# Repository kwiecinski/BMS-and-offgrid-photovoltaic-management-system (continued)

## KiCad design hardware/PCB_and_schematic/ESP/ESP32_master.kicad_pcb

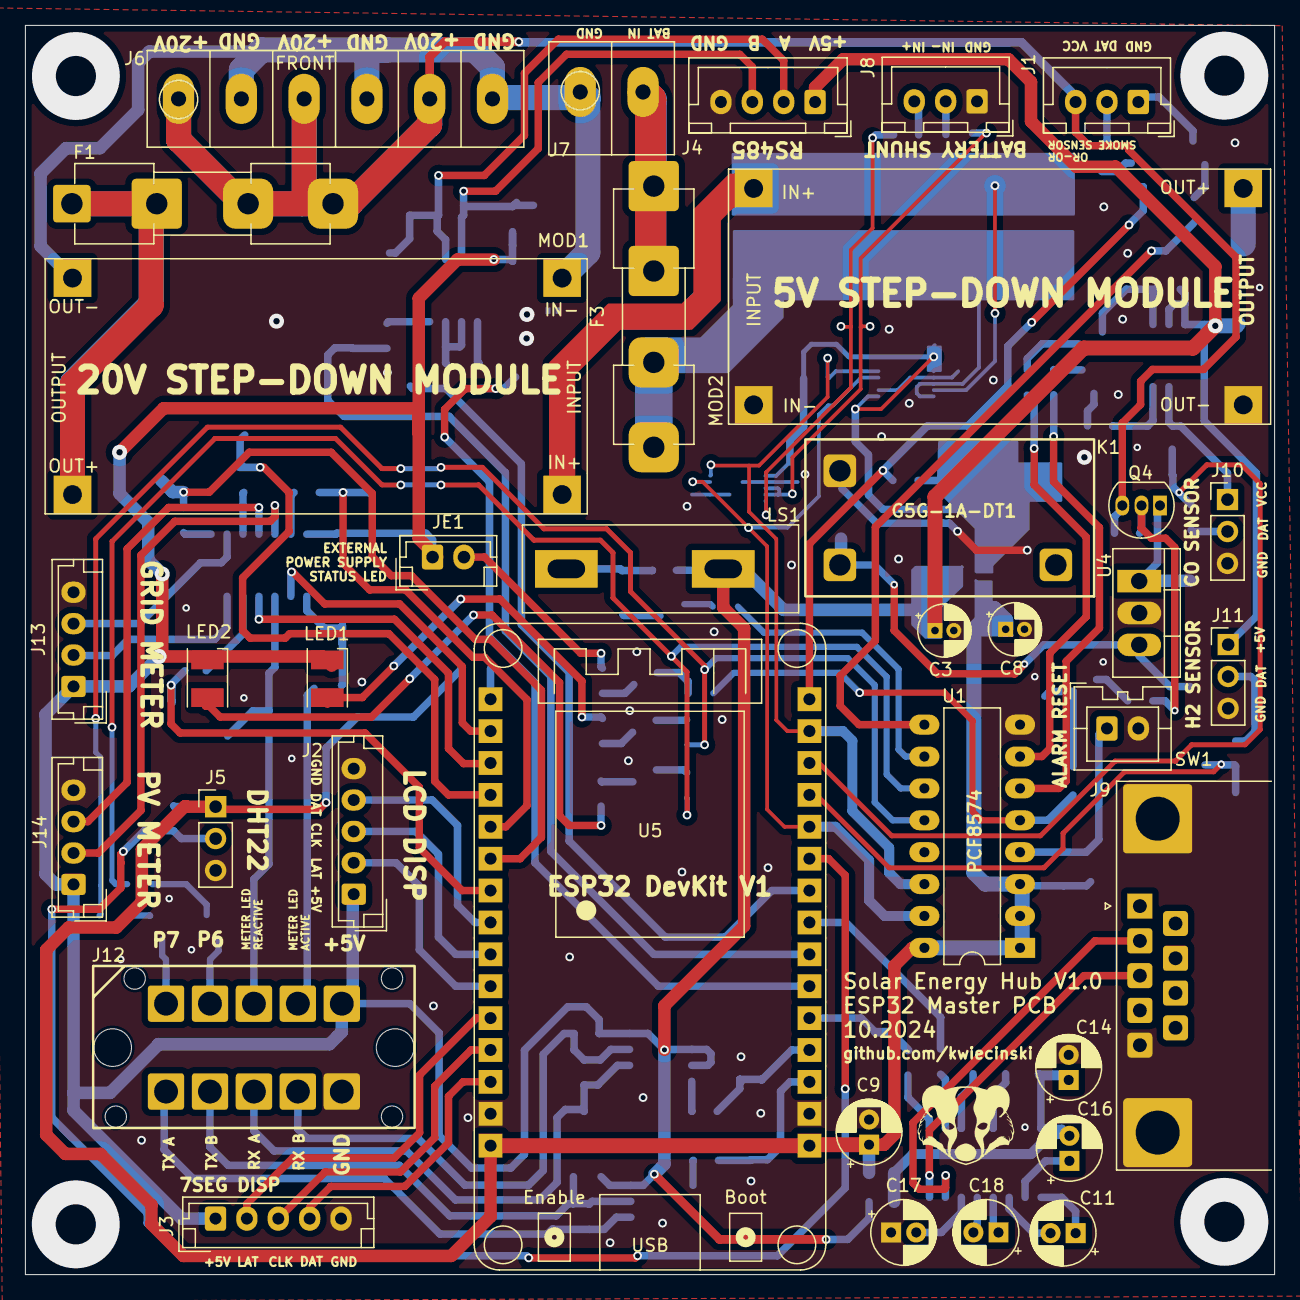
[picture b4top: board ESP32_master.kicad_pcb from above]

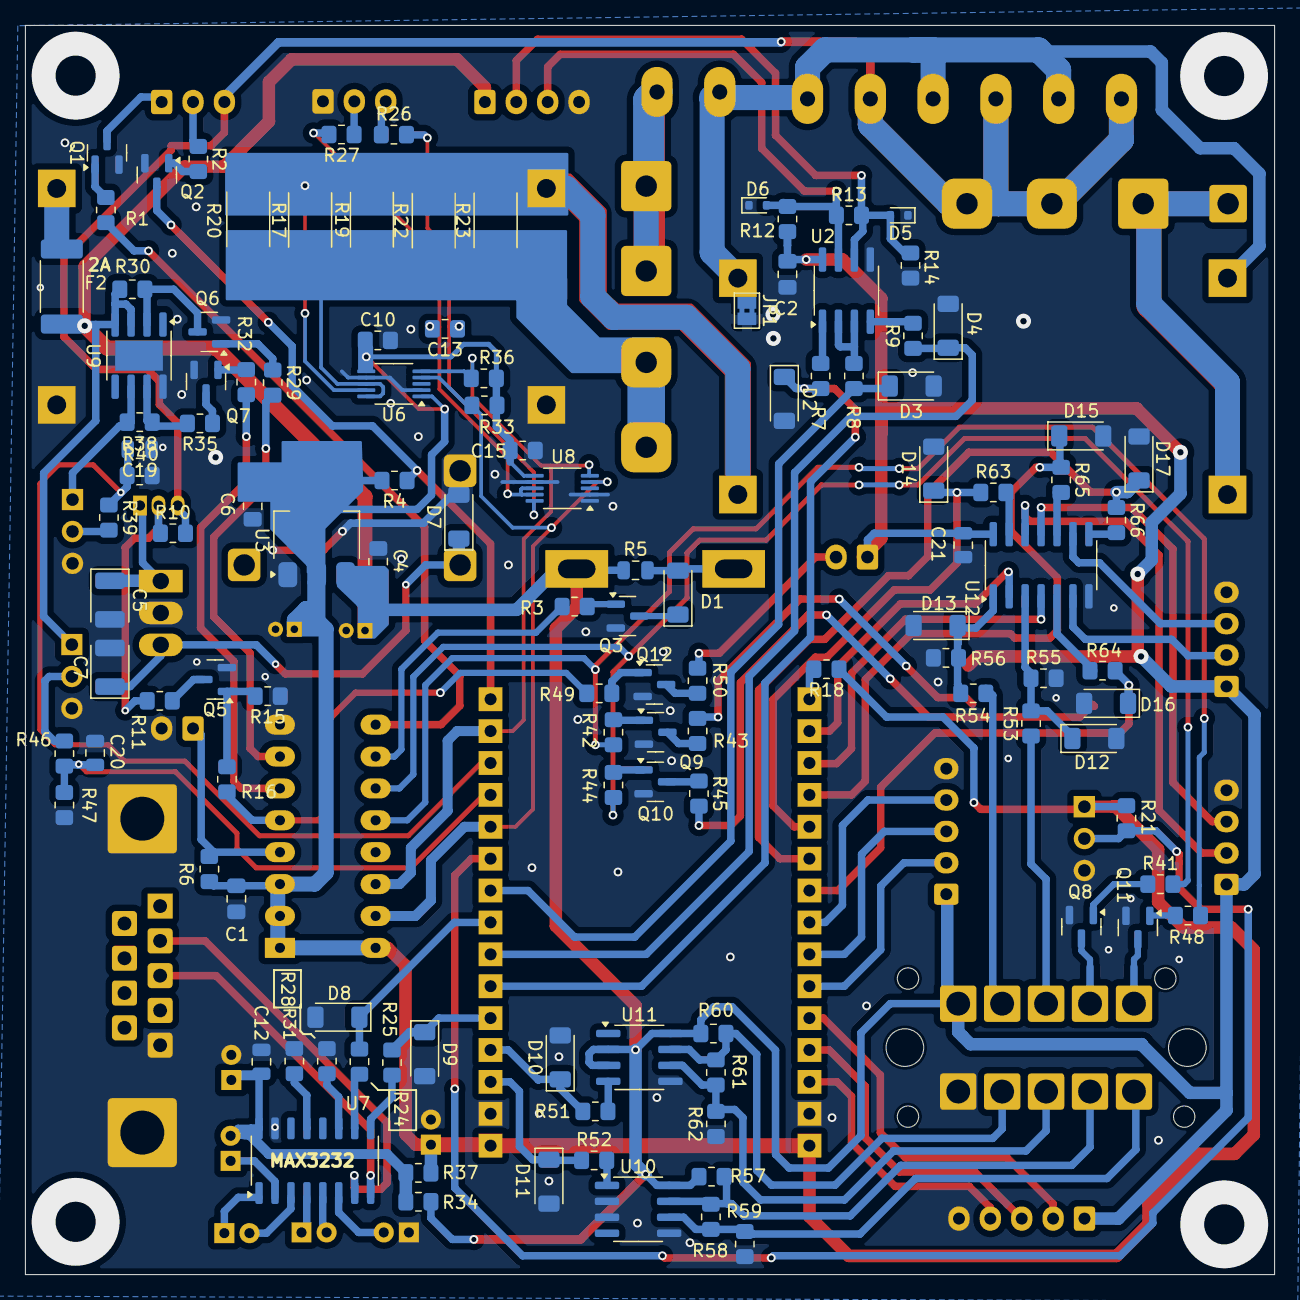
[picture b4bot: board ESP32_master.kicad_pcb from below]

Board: 2 copper layers, 99.5 x 99.5 mm, 154 parts (118 on the bottom side), 117 nets.

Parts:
C1, C2, C4, C6: 100n; C_0805_2012Metric_Pad1.18x1.45mm_HandSolder
C3: 100u; CP_Radial_D4.0mm_P1.50mm
C5: 22u/25V; CP_EIA-3528-21_Kemet-B
C7: 10u/16V; CP_EIA-3528-21_Kemet-B
C8: 22u; CP_Radial_D4.0mm_P1.50mm
C9: 22u; CP_Radial_D5.0mm_P2.00mm
C10, C15: 100n; R_0805_2012Metric_Pad1.20x1.40mm_HandSolder
C11, C16, C17, C18: 10u; CP_Radial_D5.0mm_P2.00mm
C12, C21: 100n; C_0805_2012Metric
C13: 1n; R_0805_2012Metric_Pad1.20x1.40mm_HandSolder
C14: 47u; CP_Radial_D5.0mm_P2.00mm
C19, C20: 10n; C_0805_2012Metric
D1: 1N4148; D_MiniMELF
D2, D3, D4, D8, D9, D10, D11, D14, D15, D16, D17: 3V3; D_MiniMELF
D5, D6: LESD5D5.0CT1G-MS; D_SOD-523
D7: LL4148; D_MiniMELF
D12, D13: 5V6; D_MiniMELF
F1: 2A; Fuseholder_Clip-5x20mm_Eaton_1A5601-01_Inline_P20.80x6.76mm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
F2: 2A; Fuse_2512_6332Metric_Pad1.52x3.35mm_HandSolder
F3: Fuse; Fuseholder_Clip-5x20mm_Eaton_1A5601-01_Inline_P20.80x6.76mm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
J1: OR-OR SMOKE SENSOR; JST_XH_B3B-XH-A_1x03_P2.50mm_Vertical
J2: LCD_DISP; JST_EH_B5B-EH-A_1x05_P2.50mm_Vertical
J3: 7SEG_DISP; JST_EH_B5B-EH-A_1x05_P2.50mm_Vertical
J4: RS485; JST_XH_B4B-XH-A_1x04_P2.50mm_Vertical
J5: DHT22; PinHeader_1x03_P2.54mm_Vertical
J6: DC_LINE_OUTPUT; Screw-Terminal-P6-rast-5mm-6,7x30
J7: MAIN_BATT_+24V; Screw-Terminal-P2-rast-5mm-6,7x30
J8: MAIN_BATT_SHUNT; JST_XH_B3B-XH-A_1x03_P2.50mm_Vertical
J9: DB9_Socket; DSUB-9_Female_Horizontal_P2.77x2.84mm_EdgePinOffset7.70mm_H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
J10: CO_SENSOR; PinHeader_1x03_P2.54mm_Vertical
J11: H2_SENSOR; PinHeader_1x03_P2.54mm_Vertical
J12: EXTERNAL_SIGNALS; CDDC-1,5-5-PV-3,5
J13: METER_GRID; JST_EH_B4B-EH-A_1x04_P2.50mm_Vertical
J14: METER_PV; JST_EH_B4B-EH-A_1x04_P2.50mm_Vertical
JE1: EXTERNAL_POWER_SUPPLY_STATUS; JST_EH_B2B-EH-A_1x02_P2.50mm_Vertical
JP1: Jumper_2_Bridged; SolderJumper-2_P1.3mm_Bridged2Bar_Pad1.0x1.5mm
K1: G5G-1A-DT1
LED1, LED2: LED; LED_PLCC-2_3.4x3.0mm_KA
LS1: BUZZER; Buzzer
MOD1, MOD2: LM2596-Step-Down; LM2596-Step-Down-Conv
Q1, Q2, Q3, Q5, Q8, Q9, Q10, Q11, Q12: BC817; SOT-23
Q4: BC556; TO-92_Inline
Q6, Q7: BSS138; SOT-23
R1, R2, R3, R4, R6, R11, R16, R18, R21, R30, R33, R36, R53, R54, R65, R66: 10k; R_0805_2012Metric_Pad1.20x1.40mm_HandSolder
R5: 2k; C_0805_2012Metric
R7, R8, R9, R24, R25, R51, R52, R63, R64: 4k7; R_0805_2012Metric_Pad1.20x1.40mm_HandSolder
R10, R15: 47k; R_0805_2012Metric_Pad1.20x1.40mm_HandSolder
R12, R14, R57, R59, R60, R62: 510R; R_0805_2012Metric_Pad1.20x1.40mm_HandSolder
R13, R58, R61: 120R; R_0805_2012Metric_Pad1.20x1.40mm_HandSolder
R17, R19, R20, R22, R23: 2,5mR; R_2512_6332Metric
R26, R27, R29, R32: 100R; R_0805_2012Metric_Pad1.20x1.40mm_HandSolder
R28, R31: 1k; R_0805_2012Metric_Pad1.20x1.40mm_HandSolder
R34, R37: 0R; R_0805_2012Metric_Pad1.20x1.40mm_HandSolder
R35: 1k8; R_0805_2012Metric_Pad1.20x1.40mm_HandSolder
R38, R41, R42, R44, R48, R49: 10K; R_0805_2012Metric_Pad1.20x1.40mm_HandSolder
R39, R46: 7k8; R_0805_2012Metric_Pad1.20x1.40mm_HandSolder
R40, R47: 2k2; R_0805_2012Metric_Pad1.20x1.40mm_HandSolder
R43, R45, R50: 220R; R_0805_2012Metric_Pad1.20x1.40mm_HandSolder
R55, R56: 2,4k; R_0805_2012Metric_Pad1.20x1.40mm_HandSolder
SW1: SW_Push; JST_XA_B02B-XASK-1_1x02_P2.50mm_Vertical
U1: PCF8574; DIP-16_W7.62mm_LongPads
U2: ST485; SOIC-8_3.9x4.9mm_P1.27mm
U3: AMS1117-5.0; SOT-223-3_TabPin2
U4: L7812; TO-220-3_V_Thick_Pads
U5: ESP32_DevKit_V1_DOIT; esp32_devkit_v1_doit
U6, U8: INA226; VSSOP-10_3x3mm_P0.5mm
U7: MAX3232; SO-16_3.9x9.9mm_P1.27mm
U9: UP7760; SOIC-8-1EP_3.9x4.9mm_P1.27mm_EP2.41x3.81mm
U10, U11: ST485EBDR; SOIC-8_3.9x4.9mm_P1.27mm
U12: 74HC14; SOIC-14_3.9x8.7mm_P1.27mm

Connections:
7_SEG_DISP_CLOCK: J3.3, U5.12 (IO12)
7_SEG_DISP_DATA: J3.4, U5.13 (IO13)
7_SEG_DISP_LATCH: J3.2, U5.11 (IO14)
24V_MEASURED: MOD1.2 (IN+), MOD2.2 (IN+), R17.2, R19.2, R20.2, R22.2, R23.2, U6.9 (Vin-)
+3V3: C1.1, C6.1, C8.1, C9.1, C10.1, C15.1, J5.1, R4.2, R6.2, R18.1, R21.2, R33.1, R36.1, R37.1, U1.1 (A0), U1.2 (A1), U1.3 (A2), U1.16 (VDD), U3.2 (VO), U5.15 (VIN), U5.16 (3V3), U6.1 (A1), U6.6 (VS), U8.6 (VS)
+5V: C2.1, C3.1, C4.1, C21.1, F2.2, J2.1, J3.1, J4.1, J11.1, J12.5, J13.1, J14.1, JE1.1, LED1.1 (K), LED2.1 (K), LS1.- (2), R5.1, R12.1, R30.2, R34.1, R57.2, R60.2, U2.8 (VCC), U3.3 (VI), U9.3 (VIN), U9.4 (CNTL), U10.8 (VCC), U11.2 (~RE), U11.3 (DE), U11.8 (VCC), U12.14 (VCC)
+20V: F1.1, J1.3, J6.1, J6.3, J6.5, Q4.3 (E), R10.2
+BATT_24V: F3.1, R17.1, R19.1, R20.1, R22.1, R23.1, U6.8 (Vbus), U6.10 (Vin+)
/ESP32_Measurment_Board/INV_RX_RS232: J9.2, U7.7 (T2OUT)
/ESP32_Measurment_Board/INV_TX_RS232: J9.3, U7.8 (R2IN)
/ESP32_Measurment_Board/RS485_A: D5.2 (A2), J4.2, R13.2, R14.1, U2.6 (A)
/ESP32_Measurment_Board/RS485_B: D6.2 (A2), J4.3, R12.2, R13.1, U2.7 (B)
ALARM_RESET_BUTTON: R6.1, SW1.1, U1.4 (P0)
ALARM_SYREN: R41.2, R44.2, U1.11 (P6)
ALARM_SYREN_OUTPUT: J12.2, Q8.3 (C)
BUZZER: R3.1, U1.10 (P5)
CLOCK_ESP: R36.2, U1.14 (SCL), U5.29 (IO22), U6.5 (SCL), U8.5 (SCL)
CO_SENSOR_EN: R29.2, U1.7 (P3)
CO_SENSOR_SWITCH_VOLTAGES: R32.2, U1.6 (P2)
DHT22: J5.2, R21.1, U5.25 (IO19)
EXTERNAL_PS_ON: R16.2, R49.2, U1.5 (P1)
GAMA_METER_LED_ACTIVE_ENERGY: U5.2 (SENSOR_VP), U12.2
GAMA_METER_LED_ACTIVE_ENERGY_INPUT: J12.4, R54.1
GAMA_METER_LED_REACTIVE: U5.3 (SENSOR_VN), U12.4
GAMA_METER_LED_REACTIVE_INPUT: J12.3, R53.1
GND: C1.2, C2.2, C3.2, C4.2, C5.2, C6.2, C7.2, C8.2, C9.2, C10.2, C12.1, C14.2, C15.2, C17.1, C19.1, C20.1, C21.2, D2.2 (A), D3.2 (A), D4.2 (A), D5.1 (A1), D6.1 (A1), D7.2 (A), D8.2 (A), D9.2 (A), D10.2 (A), D11.2 (A), D12.2 (A), D13.2 (A), D14.2 (A), D15.2 (A), D16.2 (A), D17.2 (A), J2.5, J3.5, J4.4, J5.3, J8.1, J9.5, J10.3, J11.3, J12.6, J13.4, J14.4, JP1.2 (B), K1.A2, MOD2.1 (IN-), MOD2.3 (OUT-), Q1.2 (E), Q2.2 (E), Q3.2 (E), Q5.2 (E), Q6.2 (S), Q7.2 (S), Q8.2 (E), Q9.2 (E), Q10.2 (E), Q11.2 (E), Q12.2 (E), R14.2, R15.1, R28.2, R31.1, R40.1, R47.1, R55.2, R56.2, R59.1, R62.1, SW1.2, U1.8 (VSS), U2.5 (GND), U3.1 (GND), U4.2 (GND), U5.14 (GND), U5.17 (GND), U6.2 (A0), U6.7 (GND), U7.15 (GND), U8.1 (A1), U8.2 (A0), U8.7 (GND), U9.8 (GND), U9.9 (EP), U10.2 (~RE), U10.3 (DE), U10.5 (GND), U11.5 (GND), U12.7 (GND)
GNDA: J6.2, J6.4, J6.6, J7.1, JP1.1 (A), MOD1.1 (IN-), MOD1.3 (OUT-)
INVERTER_RX: D8.1 (K), R24.1, U5.23 (IO5)
INVERTER_TX: D9.1 (K), R25.1, U5.20 (IO4)
LCD_DISP_CLOCK: J2.3, U5.9 (IO26)
LCD_DISP_DATA: J2.4, U5.8 (IO25)
LCD_DISP_LATCH: J2.2, U5.10 (IO27)
METER_GRID_RX: D17.1 (K), R66.1, U5.6 (IO32)
METER_GRID_TX: D16.1 (K), R64.1, U5.7 (IO33)
METER_MAIN_RX: D10.1 (K), R51.1, U5.19 (IO2)
METER_MAIN_RX_A: J12.8, R61.1, R62.2, U11.6 (A)
METER_MAIN_RX_B: J12.7, R60.1, R61.2, U11.7 (B)
METER_MAIN_TX: D11.1 (K), R52.1, U5.18 (IO15)
METER_MAIN_TX_A: J12.10, R58.1, R59.2, U10.6 (A)
METER_MAIN_TX_B: J12.9, R57.1, R58.2, U10.7 (B)
METER_PV_RX: D15.1 (K), R65.1, U5.4 (IO34)
METER_PV_TX: D14.1 (K), R63.1, U5.5 (IO35)
MQ7_CO_SENSOR: C19.2, R39.1, R40.2, U5.28 (TXD0/IO1)
MQ8_H2_SENSOR: C20.2, R46.1, R47.2, U5.27 (RXD0/IO3)
unnamed: D1.2 (A), LS1.+ (1), R5.2
unnamed: D1.1 (K), Q3.3 (C)
unnamed: C7.1, D7.1 (K), K1.A1, U4.3 (OUT)
unnamed: D12.1 (K), R53.2, R55.1, U12.3
unnamed: D13.1 (K), R54.2, R56.1, U12.1
unnamed: J1.1, Q1.3 (C)
unnamed: J1.2, R2.1
unnamed: F3.2, J7.2
unnamed: J8.2, R27.1
unnamed: J8.3, R26.1
unnamed: J10.1, R38.1, U9.6 (VOUT)
unnamed: J10.2, R39.2
unnamed: J11.2, R46.2
unnamed: J13.2, U12.6
unnamed: J13.3, U12.9
unnamed: J14.2, U12.12
unnamed: J14.3, U12.11
unnamed: JE1.2, R50.2
unnamed: LED1.2 (A), R43.2
unnamed: LED2.2 (A), R45.2
unnamed: F1.2, MOD1.4 (OUT+)
unnamed: F2.1, MOD2.4 (OUT+)
unnamed: Q1.1 (B), R1.2
unnamed: Q2.1 (B), R2.2
unnamed: Q3.1 (B), R3.2
unnamed: Q4.2 (B), R10.1, R11.2
unnamed: C5.1, Q4.1 (C), U4.1 (IN)
unnamed: Q5.1 (B), R15.2, R16.1
unnamed: Q5.3 (C), R11.1
unnamed: Q6.3 (D), R30.1, U9.2 (EN)
unnamed: Q6.1 (G), R29.1
unnamed: Q7.3 (D), R35.1
unnamed: Q7.1 (G), R32.1
unnamed: Q8.1 (B), R41.1
unnamed: Q9.1 (B), R42.1
unnamed: Q9.3 (C), R43.1
unnamed: Q10.1 (B), R44.1
unnamed: Q10.3 (C), R45.1
unnamed: Q11.1 (B), R48.1
unnamed: Q12.1 (B), R49.1
unnamed: Q12.3 (C), R50.1
unnamed: R63.2, U12.13
unnamed: R64.2, U12.5
unnamed: R65.2, U12.10
unnamed: R66.2, U12.8
unnamed: R8.2, U2.2 (~RE), U2.3 (DE)
unnamed: R9.2, U2.4 (DI)
unnamed: R7.2, U2.1 (RO)
unnamed: R18.2, U5.1 (EN)
unnamed: C11.1, U7.1 (C1+)
unnamed: C11.2, U7.3 (C1-)
unnamed: C18.1, U7.4 (C2+)
unnamed: C18.2, U7.5 (C2-)
unnamed: R31.2, U7.13 (R1IN)
unnamed: R25.2, U7.9 (R2OUT)
unnamed: R28.1, U7.11 (T1IN)
unnamed: R24.2, U7.10 (T2IN)
unnamed: C12.2, C14.1, C16.2, R34.2, R37.2, U7.16 (VCC)
unnamed: C16.1, U7.2 (VS+)
unnamed: C17.2, U7.6 (VS-)
unnamed: C13.2, R27.2, U8.8 (Vbus), U8.9 (Vin-)
unnamed: C13.1, R26.2, U8.10 (Vin+)
unnamed: R35.2, R38.2, U9.7 (FB)
unnamed: R52.2, U10.1 (RO)
unnamed: R51.2, U11.4 (DI)
P7_UNCONNECTED: R42.2, R48.2, U1.12 (P7)
P7_UNCONNECTED_OUTPUT: J12.1, Q11.3 (C)
RS485_OUTPUT_ENABLE_ESP: D3.1 (K), R8.1, U5.24 (IO18)
RS485_RX_ESP: D2.1 (K), R7.1, U5.21 (IO16)
RS485_TX_ESP: D4.1 (K), R9.1, U5.22 (IO17)
SDA_ESP: R33.2, U1.15 (SDA), U5.26 (IO21), U6.4 (SDA), U8.4 (SDA)
SMOKE_DETECTOR_OUTPUT: Q2.3 (C), R4.1, U5.30 (IO23)
SMOKE_DETECTOR_RESET: R1.1, U1.9 (P4)

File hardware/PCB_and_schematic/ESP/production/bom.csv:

Designator,Footprint,Quantity,Value,LCSC Part #
"C1, C10, C12, C15, C2, C21, C4, C6",0805,8,100n,
"C11, C16, C17, C18",CP_Radial_D5.0mm_P2.00mm,4,10u,
C13,0805,1,1n,
C14,CP_Radial_D5.0mm_P2.00mm,1,47u,
"C19, C20",0805,2,10n,
C3,CP_Radial_D4.0mm_P1.50mm,1,100u,
C5,CP_EIA-3528-21_Kemet-B,1,22u/25V,
C7,CP_EIA-3528-21_Kemet-B,1,10u/16V,
C8,CP_Radial_D4.0mm_P1.50mm,1,22u,
C9,CP_Radial_D5.0mm_P2.00mm,1,22u,
D1,D_MiniMELF,1,1N4148,
"D10, D11, D14, D15, D16, D17, D2, D3, D4, D8, D9",D_MiniMELF,11,3V3,
"D12, D13",D_MiniMELF,2,5V6,
"D5, D6",D_SOD-523,2,LESD5D5.0CT1G-MS,
D7,D_MiniMELF,1,LL4148,
F1,Fuseholder_Clip-5x20mm_Eaton_1A5601-01_Inline_P20.80x6.76mm_D1.70mm_Horizontal,1,2A,
F2,2512,1,2A,
F3,Fuseholder_Clip-5x20mm_Eaton_1A5601-01_Inline_P20.80x6.76mm_D1.70mm_Horizontal,1,Fuse,
J1,JST_XH_B3B-XH-A_1x03_P2.50mm_Vertical,1,OR-OR SMOKE SENSOR,
J10,PinHeader_1x03_P2.54mm_Vertical,1,CO_SENSOR,
J11,PinHeader_1x03_P2.54mm_Vertical,1,H2_SENSOR,
J12,"CDDC-1,5-5-PV-3,5",1,EXTERNAL_SIGNALS,
J13,JST_EH_B4B-EH-A_1x04_P2.50mm_Vertical,1,METER_GRID,
J14,JST_EH_B4B-EH-A_1x04_P2.50mm_Vertical,1,METER_PV,
J2,JST_EH_B5B-EH-A_1x05_P2.50mm_Vertical,1,LCD_DISP,
J3,JST_EH_B5B-EH-A_1x05_P2.50mm_Vertical,1,7SEG_DISP,
J4,JST_XH_B4B-XH-A_1x04_P2.50mm_Vertical,1,RS485,
J5,PinHeader_1x03_P2.54mm_Vertical,1,DHT22,
J6,"Screw-Terminal-P6-rast-5mm-6,7x30",1,DC_LINE_OUTPUT,
J7,"Screw-Terminal-P2-rast-5mm-6,7x30",1,MAIN_BATT_+24V,
J8,JST_XH_B3B-XH-A_1x03_P2.50mm_Vertical,1,MAIN_BATT_SHUNT,
J9,DSUB-9_Female_Horizontal_P2.77x2.84mm_EdgePinOffset7.70mm_Housed_MountingHolesOffset9.12mm,1,DB9_Socket,
JE1,JST_EH_B2B-EH-A_1x02_P2.50mm_Vertical,1,EXTERNAL_POWER_SUPPLY_STATUS,
JP1,SolderJumper-2_P1.3mm_Bridged2Bar_Pad1.0x1.5mm,1,Jumper_2_Bridged,
K1,G5G-1A-DT1,1,G5G-1A-DT1,
"LED1, LED2",LED_PLCC-2_3.4x3.0mm_KA,2,LED,
LS1,Buzzer,1,BUZZER,
"MOD1, MOD2",LM2596-Step-Down-Conv,2,LM2596-Step-Down,
"Q1, Q10, Q11, Q12, Q2, Q3, Q5, Q8, Q9",SOT-23,9,BC817,
Q4,TO-92_Inline,1,BC556,
"Q6, Q7",SOT-23,2,BSS138,
"R1, R11, R16, R18, R2, R21, R3, R30, R33, R36, R38, R4, R41, R42, R44, R48, R49, R53, R54, R6, R65, R66",0805,22,10k,
"R10, R15",0805,2,47k,
"R12, R14, R57, R59, R60, R62",0805,6,510R,
"R13, R58, R61",0805,3,120R,
"R17, R19, R20, R22, R23",2512,5,"2,5mR",
"R24, R25, R51, R52, R63, R64, R7, R8, R9",0805,9,4k7,
"R26, R27, R29, R32",0805,4,100R,
"R28, R31",0805,2,1k,
"R34, R37",0805,2,0R,
R35,0805,1,1k8,
"R39, R46",0805,2,7k8,
"R40, R47",0805,2,2k2,
"R43, R45, R50",0805,3,220R,
R5,0805,1,2k,
"R55, R56",0805,2,"2,4k",
SW1,JST_XA_B02B-XASK-1_1x02_P2.50mm_Vertical,1,SW_Push,
U1,DIP-16_W7.62mm_LongPads,1,PCF8574,
"U10, U11",SOIC-8_3.9x4.9mm_P1.27mm,2,ST485EBDR,
U12,SOIC-14_3.9x8.7mm_P1.27mm,1,74HC14,
U2,SOIC-8_3.9x4.9mm_P1.27mm,1,ST485,
U3,SOT-223-3_TabPin2,1,AMS1117-5.0,
U4,TO-220-3_V_Thick_Pads,1,L7812,
U5,esp32_devkit_v1_doit,1,ESP32_DevKit_V1_DOIT,
"U6, U8",VSSOP-10_3x3mm_P0.5mm,2,INA226,
U7,SO-16_3.9x9.9mm_P1.27mm,1,MAX3232,
U9,SOIC-8-1EP_3.9x4.9mm_P1.27mm_EP2.41x3.81mm,1,UP7760,

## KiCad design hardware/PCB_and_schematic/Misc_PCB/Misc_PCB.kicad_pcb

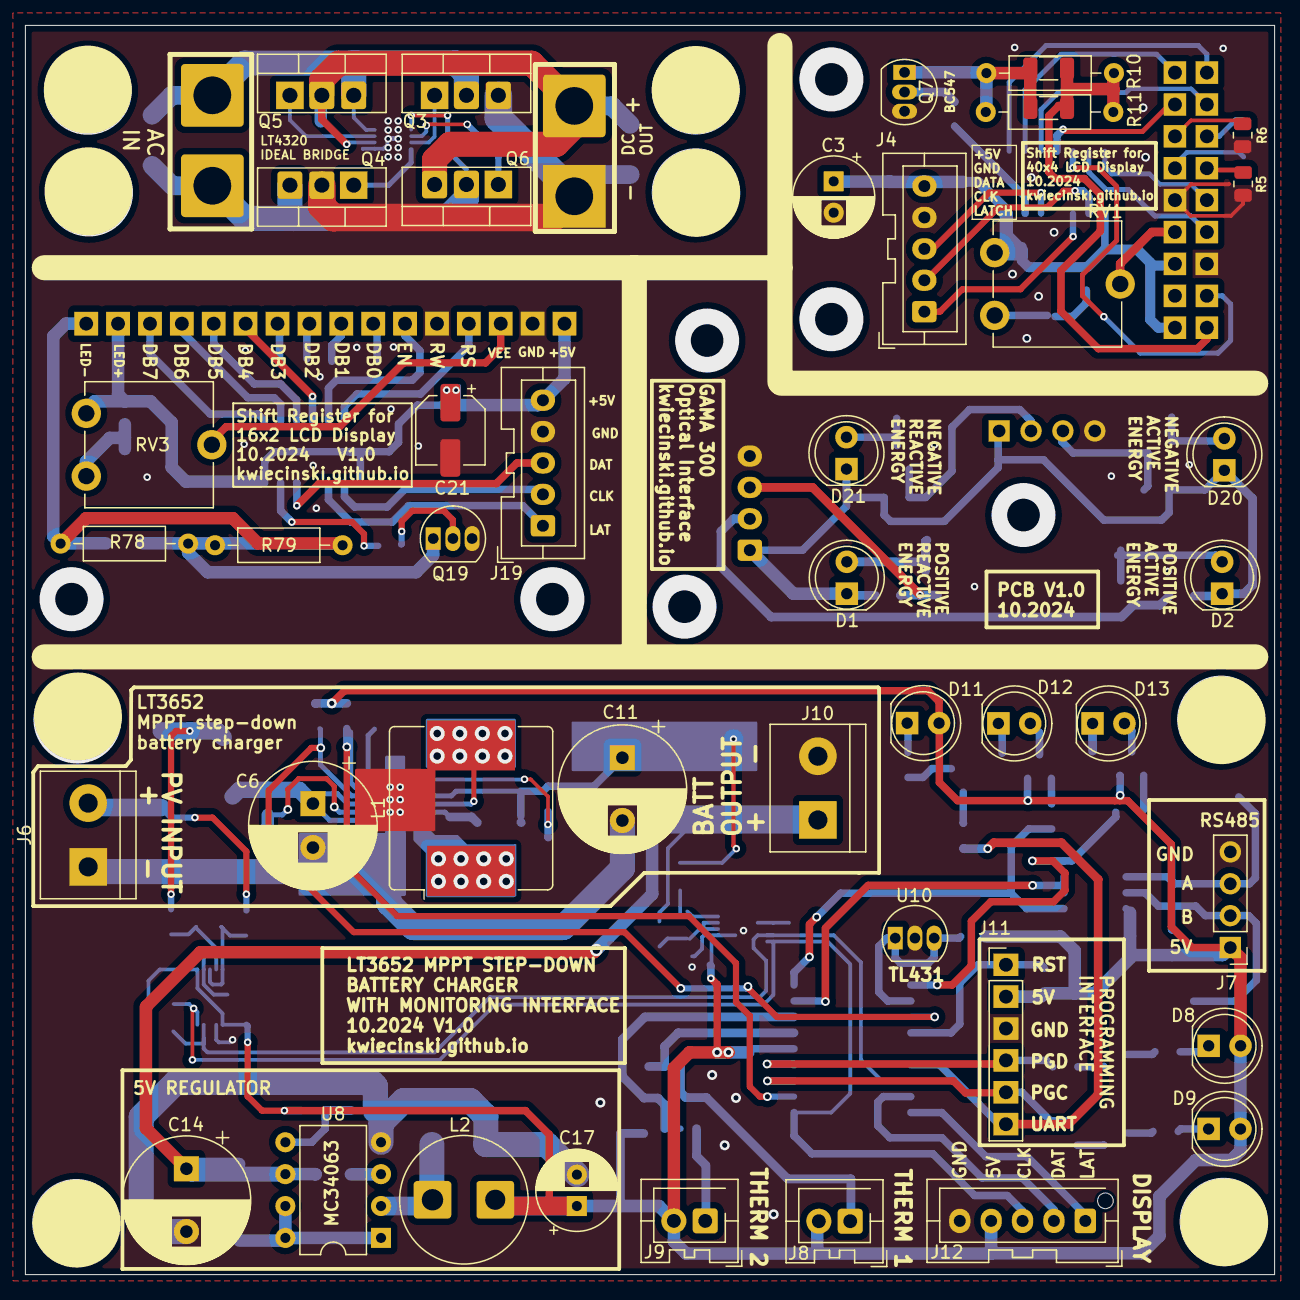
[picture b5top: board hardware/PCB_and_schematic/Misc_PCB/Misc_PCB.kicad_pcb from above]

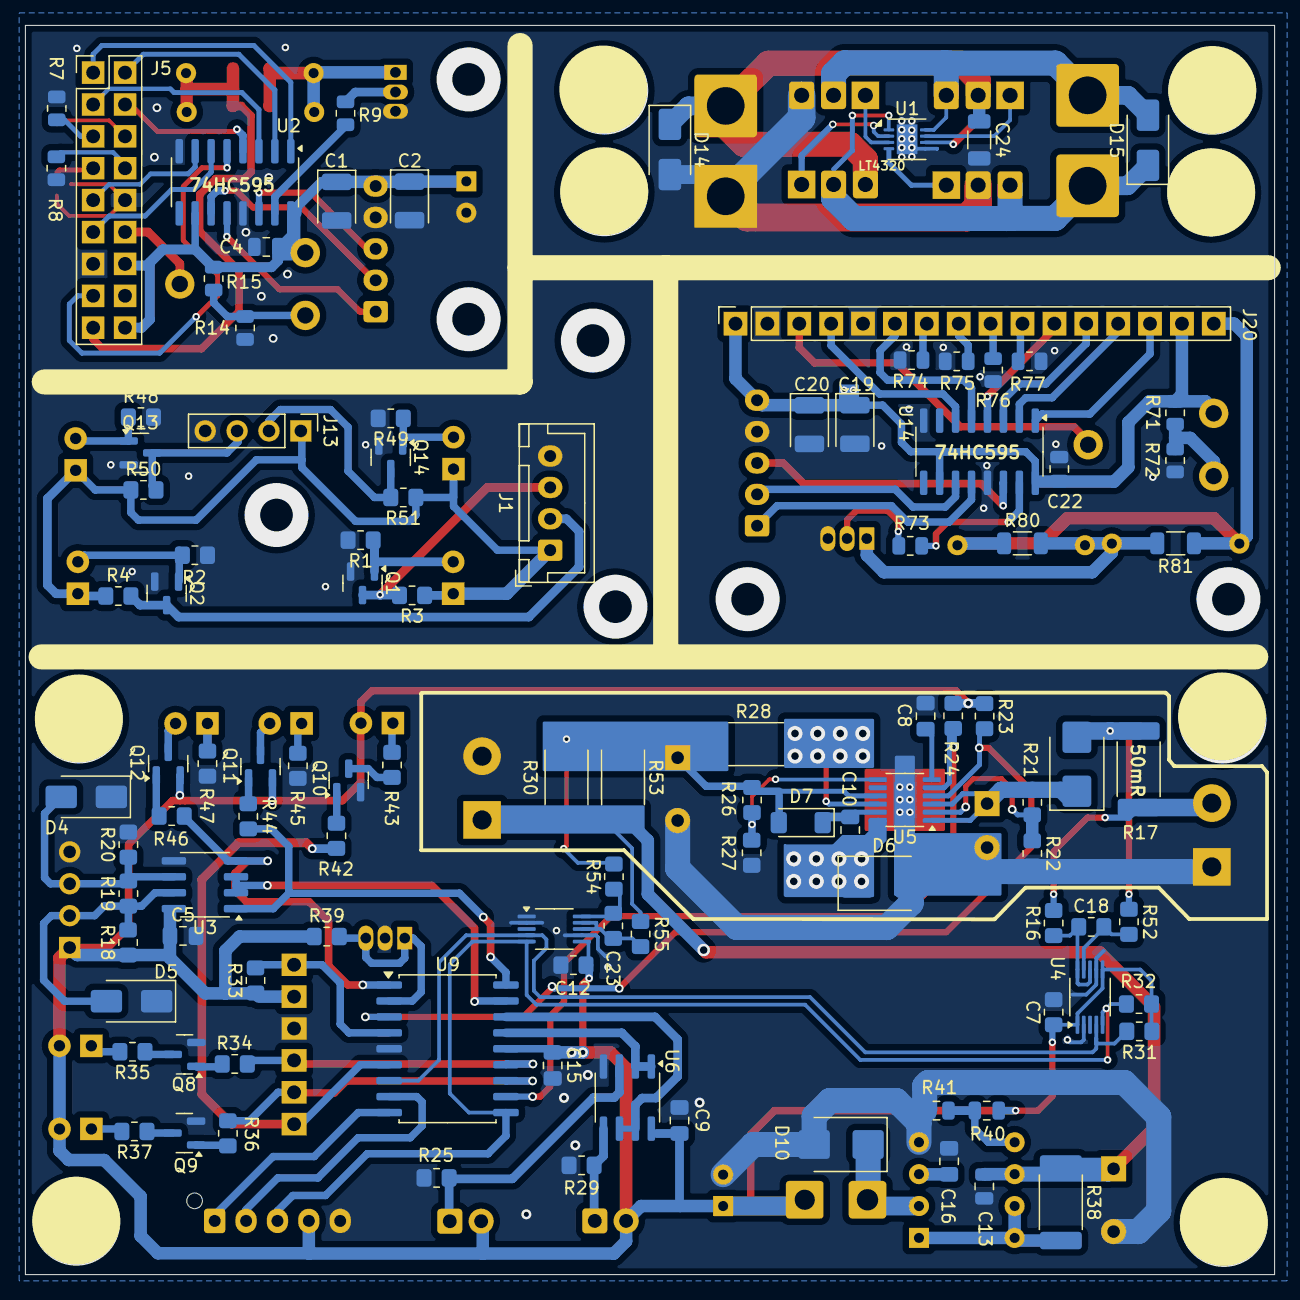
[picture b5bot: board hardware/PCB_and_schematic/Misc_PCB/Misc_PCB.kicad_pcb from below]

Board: 2 copper layers, 99.5 x 99.5 mm, 152 parts (106 on the bottom side), 110 nets.

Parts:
C1, C2, C19, C20: 470u/6,3V; CP_EIA-3528-21_Kemet-B
C3: 470u/6,3V; CP_Radial_D6.3mm_P2.50mm
C4, C13, C22: 100n; C_0805_2012Metric
C5, C9, C15: 100n; C_0805_2012Metric_Pad1.18x1.45mm_HandSolder
C6: 470u/40V; CP_Radial_D10.0mm_P3.50mm
C7, C12, C18, C23: 100n; R_0805_2012Metric_Pad1.20x1.40mm_HandSolder
C8: 0R; C_0805_2012Metric_Pad1.18x1.45mm_HandSolder
C10: 1u/10V; C_0805_2012Metric_Pad1.18x1.45mm_HandSolder
C11: 470u/16V; CP_Radial_D10.0mm_P5.00mm
C14: 670u/35V; CP_Radial_D10.0mm_P5.00mm
C16: 100p; C_0805_2012Metric_Pad1.18x1.45mm_HandSolder
C17: 560u/6,3V; CP_Radial_D6.3mm_P2.50mm
C21: 470u/6,3V; CP_Elec_5x5.7
C24: 1u/100v; C_1206_3216Metric
D1, D2, D20, D21: BPV10; LED_D5.0mm
D3, D6, D10: D_Schottky; D_SMB
D4, D5: D_TVS; D_SMA
D7: 1N4148; D_MiniMELF
D8, D9, D11, D12, D13: LED; LED_D5.0mm
D14: SMAJ60A; D_SMA
D15: SMAJ60CA; D_SMA
J1: DIODE_BLINK_METER; JST_XH_B4B-XH-A_1x04_P2.50mm_Vertical
J2: AC_IN; SolderWire-2.5sqmm_1x02_P7.2mm_D2.4mm_OD3.6mm
J3: DC_OUT; SolderWire-2.5sqmm_1x02_P7.2mm_D2.4mm_OD3.6mm
J4, J19: LCD_CONN; JST_XA_B05B-XASK-1_1x05_P2.50mm_Vertical
J5: LCD_DISPLAY; PinHeader_2x09_P2.54mm_Vertical
J6: SOLAR_PANEL; TerminalBlock_bornier-2_P5.08mm
J7: RS485; PinHeader_1x04_P2.54mm_Vertical
J8, J9: THERMISTOR; JST_XA_B02B-XASK-1-A_1x02_P2.50mm_Vertical
J10: BATT; TerminalBlock_bornier-2_P5.08mm
J11: ICP; PinHeader_1x06_P2.54mm_Vertical
J12: LCD_DISPLAY; JST_XA_B05B-XASK-1-A_1x05_P2.50mm_Vertical
J13: DIODE_BLINK_METER_OUT; PinHeader_1x04_P2.54mm_Vertical
J20: LCD16x2; PinSocket_1x16_P2.54mm_Vertical
L1: L; L_Bourns_SRR1208_12.7x12.7mm
L2: 220uH; L_Radial_D10.0mm_P5.00mm_Fastron_07P
Q1, Q2, Q8, Q9, Q10, Q13, Q14: BC817; SOT-23
Q3, Q4, Q5, Q6: IRF540N; TO-220-3_Vertical-little-bigger pads
Q7, Q19: BC547; TO-92_Inline_LITTLE_BIGGER
Q11, Q12: BC807; SOT-23
R1, R2, R48, R49: 47k; R_0805_2012Metric_Pad1.20x1.40mm_HandSolder
R3, R4, R50, R51: 22k; R_0805_2012Metric_Pad1.20x1.40mm_HandSolder
R5, R6, R7, R8, R9, R15, R71, R73, R74, R75, R76, R77: 10k; R_0805_2012Metric
R10, R11, R78, R79: R; R_Axial_DIN0207_L6.3mm_D2.5mm_P10.16mm_Horizontal
R12, R13, R80, R81: R; R_1206_3216Metric
R14, R72: 39k; R_0805_2012Metric
R16, R52, R54, R55: 10R; R_0805_2012Metric_Pad1.20x1.40mm_HandSolder
R17, R30: 50m; R_2512_6332Metric_Pad1.40x3.35mm_HandSolder
R18, R20, R21, R22: 510R; R_0805_2012Metric_Pad1.20x1.40mm_HandSolder
R19: 120R; R_0805_2012Metric_Pad1.20x1.40mm_HandSolder
R23, R24, R31, R32, R33: 10k; R_0805_2012Metric_Pad1.20x1.40mm_HandSolder
R25, R29: 100K; R_0805_2012Metric_Pad1.20x1.40mm_HandSolder
R26, R27: 100k; R_0805_2012Metric_Pad1.20x1.40mm_HandSolder
R28: 50mR; R_2512_6332Metric_Pad1.40x3.35mm_HandSolder
R34, R36, R42, R44, R46: 10K; R_0805_2012Metric_Pad1.20x1.40mm_HandSolder
R35, R37, R43, R45, R47: 220R; R_0805_2012Metric_Pad1.20x1.40mm_HandSolder
R38: 500m; R_2512_6332Metric_Pad1.40x3.35mm_HandSolder
R39: 1k; R_0805_2012Metric_Pad1.20x1.40mm_HandSolder
R40: 10k; C_0805_2012Metric
R41: 3k3; C_0805_2012Metric
R53: 100m; R_2512_6332Metric_Pad1.40x3.35mm_HandSolder
RV1, RV3: 10k; Potentiometer_ACP_CA9-V10_Vertical
U1: LT4320xDD-1; DFN-8-1EP_3x3mm_P0.5mm_EP1.65x2.38mm
U2, U14: 74HC595; SOIC-16_3.9x9.9mm_P1.27mm
U3: ST485; SOIC-8_3.9x4.9mm_P1.27mm
U4, U7: INA226; VSSOP-10_3x3mm_P0.5mm
U5: LT3652EMSE; MSOP-12-1EP_3x4mm_P0.65mm_EP1.65x2.85mm
U6: LM358; SOIC-8_3.9x4.9mm_P1.27mm
U8: MC34063AP; DIP-8_W7.62mm
U9: PIC16F819-ISO; SOIC-18W_7.5x11.6mm_P1.27mm
U10: TL431LP; TO-92_Inline_LITTLE_BIGGER

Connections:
+5V: C1.1, C2.1, C3.1, C4.1, C5.1, C7.1, C9.1, C12.1, C15.1, C17.1, C19.1, C20.1, C21.1, C22.1, D1.1 (K), D2.1 (K), D8.2 (A), D9.2 (A), D11.2 (A), D20.1 (K), D21.1 (K), J1.1, J4.5, J5.14, J5.18, J7.1, J8.2, J9.2, J11.2, J12.4, J13.1, J19.5, J20.1, J20.15, L2.2, Q11.2 (E), Q12.2 (E), R3.1, R4.1, R15.2, R18.1, R23.1, R24.1, R31.1, R32.1, R33.1, R39.1, R40.1, R50.1, R51.1, R71.2, RV1.3, RV3.3, U2.10 (~SRCLR), U2.16 (VCC), U3.8 (VCC), U4.1 (A1), U4.6 (VS), U6.8 (V+), U7.6 (VS), U9.14 (VDD), U14.10 (~SRCLR), U14.16 (VCC)
/LT3652 MPPT/RS485_A: D4.2 (A2), J7.3, R19.2, R20.1, U3.6 (A)
/LT3652 MPPT/RS485_B: D5.2 (A2), J7.2, R18.2, R19.1, U3.7 (B)
/Shift Register for 16x2 LCD Display/CLK: J19.2, U14.11 (SRCLK)
/Shift Register for 16x2 LCD Display/DATA: J19.3, U14.14 (SER)
/Shift Register for 16x2 LCD Display/LATCH: J19.1, U14.12 (RCLK)
/Shift Register for 40x4 LCD Display/CLK: J4.2, U2.11 (SRCLK)
/Shift Register for 40x4 LCD Display/DATA: J4.3, U2.14 (SER)
/Shift Register for 40x4 LCD Display/LATCH: J4.1, U2.12 (RCLK)
BACKLIGHT_DRIVE: R9.1, U2.15 (QA)
BACKLIGHT_DRIVE_A: R73.1, U14.15 (QA)
BATT_CURRENT_HIGH: C11.1, D7.2 (A), R26.2, R28.2, R30.1, R53.1, R54.2, U5.9 (BAT)
BATT_CURRENT_LOW: C13.1, C14.1, J10.1, R30.2, R38.1, R53.2, R55.1, U8.6 (Vin)
CHRG: R23.2, U5.4 (~CHRG), U9.3 (T0CKL/AN4/RA4)
DATA: J12.2, U9.8 (RB2/SDO/CCP1)
DB0: J5.8, R8.2
DB1: J5.7, R5.2
DB2: J5.6, R6.2
DB3: J5.5, R7.2
DB4: J5.4, U2.4 (QE)
DB4_A: J20.11, U14.4 (QE)
DB5: J5.3, U2.3 (QD)
DB5_A: J20.12, U14.3 (QD)
DB6: J5.2, U2.2 (QC)
DB6_A: J20.13, U14.2 (QC)
DB7: J5.1, U2.1 (QB)
DB7_A: J20.14, U14.1 (QB)
DBG_UART: J11.6, R42.2, U9.6 (RB0/INT)
E1: J5.9, U2.7 (QH)
E2: J5.15, U2.5 (QF)
EN: J20.6, U14.5 (QF)
FAULT: R24.2, U5.5 (~FAULT), U9.11 (RB5/~SS)
GND: C1.2, C2.2, C3.2, C4.2, C5.2, C6.2, C7.2, C8.2, C9.2, C11.2, C12.2, C13.2, C14.2, C15.2, C16.2, C17.2, C19.2, C20.2, C21.2, C22.2, C24.2, D4.1 (A1), D5.1 (A1), D6.2 (A), D10.2 (A), D14.2 (A2), J1.4, J3.2, J4.4, J5.10, J5.13, J6.1, J7.4, J10.2, J11.3, J12.5, J13.4, J19.4, J20.2, J20.5, Q1.2 (E), Q2.2 (E), Q3.3 (S), Q4.2 (D), Q7.3 (E), Q8.2 (E), Q9.2 (E), Q10.2 (E), Q13.2 (E), Q14.2 (E), Q19.3 (E), R1.2, R2.2, R5.1, R6.1, R7.1, R8.1, R14.2, R20.2, R22.2, R25.2, R27.1, R29.2, R41.2, R45.1, R47.1, R48.2, R49.2, R72.2, R74.1, R75.1, R76.1, R77.1, U1.5 (OUTN), U1.9 (OUTN), U2.8 (GND), U2.13 (~OE), U3.5 (GND), U4.2 (A0), U4.7 (GND), U5.13 (GND), U6.4 (V-), U7.1 (A1), U7.2 (A0), U7.7 (GND), U8.4 (GND), U9.5 (VSS), U10.2 (A), U14.8 (GND), U14.13 (~OE)
LATCH: J12.1, U9.9 (RB3/CCP1/PGM)
unnamed: D1.2 (A), Q1.1 (B), R1.1
unnamed: D2.2 (A), Q2.1 (B), R2.1
unnamed: C6.1, D3.1 (K), R21.1, U5.1 (V_{IN}), U5.3 (~SHDN)
unnamed: C10.1, D6.1 (K), L1.1, U5.12 (SW)
unnamed: C10.2, D7.1 (K), U5.11 (BOOST)
unnamed: D8.1 (K), R35.2
unnamed: D9.1 (K), R37.2
unnamed: D10.1 (K), L2.1, U8.2 (SwE)
unnamed: D11.1 (K), R43.2
unnamed: D12.2 (A), Q11.3 (C)
unnamed: D12.1 (K), R45.2
unnamed: D13.2 (A), Q12.3 (C)
unnamed: D13.1 (K), R47.2
unnamed: C24.1, D14.1 (A1), J3.1, Q5.2 (D), Q6.3 (S), U1.6 (OUTP)
unnamed: D15.1 (A1), J2.1, Q4.3 (S), Q6.2 (D), U1.1 (IN2)
unnamed: D15.2 (A2), J2.2, Q3.2 (D), Q5.3 (S), U1.8 (IN1)
unnamed: D20.2 (A), Q13.1 (B), R48.1
unnamed: D21.2 (A), Q14.1 (B), R49.1
unnamed: J1.2, Q2.3 (C), R4.2
unnamed: J1.3, Q1.3 (C), R3.2
unnamed: J5.12, RV1.2
unnamed: J5.17, R10.1, R11.1, R12.1, R13.1
unnamed: J8.1, R25.1, U6.3 (+)
unnamed: J9.1, R29.1, U6.5 (+)
unnamed: J13.2, Q14.3 (C), R51.2
unnamed: J13.3, Q13.3 (C), R50.2
unnamed: J20.3, RV3.2
unnamed: J20.7, R74.2
unnamed: J20.8, R75.2
unnamed: J20.9, R76.2
unnamed: J20.10, R77.2
unnamed: J20.16, R78.1, R79.1, R80.1, R81.1
unnamed: Q3.1 (G), U1.3 (BG2)
unnamed: Q4.1 (G), U1.4 (BG1)
unnamed: Q5.1 (G), U1.7 (TG1)
unnamed: Q6.1 (G), U1.2 (TG2)
unnamed: Q7.2 (B), R9.2
unnamed: Q7.1 (C), R10.2, R11.2, R12.2, R13.2
unnamed: Q8.1 (B), R34.1
unnamed: Q8.3 (C), R35.1
unnamed: Q9.1 (B), R36.1
unnamed: Q9.3 (C), R37.1
unnamed: Q10.1 (B), R42.1
unnamed: Q10.3 (C), R43.1
unnamed: Q11.1 (B), R44.1
unnamed: Q12.1 (B), R46.1
unnamed: Q19.2 (B), R73.2
unnamed: Q19.1 (C), R78.2, R79.2, R80.2, R81.2
unnamed: R14.1, R15.1, RV1.1
unnamed: R71.1, R72.1, RV3.1
unnamed: C18.1, R16.1, U4.8 (Vbus), U4.10 (Vin+)
unnamed: C18.2, R52.2, U4.9 (Vin-)
unnamed: L1.2, R28.1, U5.10 (SENSE)
unnamed: C8.1, U5.6 (TIMER)
unnamed: R26.1, R27.2, U5.7 (V_{FB})
unnamed: R21.2, R22.1, U5.2 (V_{IN_REG})
unnamed: C23.2, R55.2, U7.8 (Vbus), U7.9 (Vin-)
unnamed: C23.1, R54.1, U7.10 (Vin+)
unnamed: R38.2, U8.1 (SwC), U8.7 (Ipk), U8.8 (DC)
unnamed: C16.1, U8.3 (TC)
unnamed: R40.2, R41.1, U8.5 (Vfb)
PGC: J11.5, R36.2, U9.12 (RB6/T1OSO/T1CKI/PGC)
PGD: J11.4, R34.2, U9.13 (RB7/T1OSI/PGD)
RS: J5.11, U2.6 (QG)
RS232_RX: R44.2, U3.1 (RO), U9.18 (AN1/RA1)
RS232_TX: R46.2, U3.4 (DI), U9.1 (Vref-/AN2/RA2)
RS485_OUTPUT_ENABLE: U3.2 (~RE), U3.3 (DE), U9.17 (AN0/RA0)
RST: J11.1, R33.2, U9.4 (Vpp/~MCLR/RA5)
RS_A: J20.4, U14.6 (QG)
SCL_SCK: J12.3, R32.2, U4.5 (SCL), U7.5 (SCL), U9.10 (RB4/SCK/SCL)
SDA: R31.2, U4.4 (SDA), U7.4 (SDA), U9.7 (RB1/SDI/SDA)
SOLAR_CURRENT_HIGH: J6.2, R16.2, R17.1
SOLAR_CURRENT_LOW: D3.2 (A), R17.2, R52.1
TEMP1: U6.1, U6.2 (-), U9.15 (CLKO/OSC2/RA6)
TEMP2: U6.6 (-), U6.7, U9.16 (CLKI/OSC1/RA7)
VREF_2V5: R39.2, U9.2 (Vref+/AN3/RA3), U10.1 (REF), U10.3 (K)

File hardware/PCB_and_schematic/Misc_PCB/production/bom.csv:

Designator,Footprint,Quantity,Value,LCSC Part #
"C1, C19, C2, C20",CP_EIA-3528-21_Kemet-B,4,"470u/6,3V",
C10,0805,1,1u/10V,
C11,CP_Radial_D10.0mm_P5.00mm,1,470u/16V,
"C12, C13, C15, C18, C22, C23, C4, C5, C7, C9",0805,10,100n,
C14,CP_Radial_D10.0mm_P5.00mm,1,670u/35V,
C16,0805,1,100p,
C17,CP_Radial_D6.3mm_P2.50mm,1,"560u/6,3V",
C21,CP_Elec_5x5.7,1,"470u/6,3V",
C3,CP_Radial_D6.3mm_P2.50mm,1,"470u/6,3V",
C6,CP_Radial_D10.0mm_P3.50mm,1,470u/40V,
C8,0805,1,0R,
"D1, D2, D20, D21",LED_D5.0mm,4,BPV10,
"D10, D3, D6",D_SMB,3,D_Schottky,
"D11, D12, D13, D8, D9",LED_D5.0mm,5,LED,
"D4, D5",D_SMA,2,D_TVS,
D7,D_MiniMELF,1,1N4148,
J1,JST_XH_B4B-XH-A_1x04_P2.50mm_Vertical,1,DIODE_BLINK_METER,
J10,TerminalBlock_bornier-2_P5.08mm,1,BATT,
J11,PinHeader_1x06_P2.54mm_Vertical,1,ICP,
J12,JST_XA_B05B-XASK-1-A_1x05_P2.50mm_Vertical,1,LCD_DISPLAY,
J13,PinHeader_1x04_P2.54mm_Vertical,1,DIODE_BLINK_METER_OUT,
"J19, J4",JST_XA_B05B-XASK-1_1x05_P2.50mm_Vertical,2,LCD_CONN,
J2,SolderWire-2.5sqmm_1x02_P7.2mm_D2.4mm_OD3.6mm,1,AC_IN,
J20,PinSocket_1x16_P2.54mm_Vertical,1,LCD16x2,
J3,SolderWire-2.5sqmm_1x02_P7.2mm_D2.4mm_OD3.6mm,1,DC_OUT,
J5,PinHeader_2x09_P2.54mm_Vertical,1,LCD_DISPLAY,
J6,TerminalBlock_bornier-2_P5.08mm,1,SOLAR_PANEL,
J7,PinHeader_1x04_P2.54mm_Vertical,1,RS485,
"J8, J9",JST_XA_B02B-XASK-1-A_1x02_P2.50mm_Vertical,2,THERMISTOR,
L1,L_Bourns_SRR1208_12.7x12.7mm,1,L,
L2,L_Radial_D10.0mm_P5.00mm_Fastron_07P,1,220uH,
"Q1, Q10, Q13, Q14, Q2, Q8, Q9",SOT-23,7,BC817,
"Q11, Q12",SOT-23,2,BC807,
"Q19, Q7",TO-92_Inline_LITTLE_BIGGER,2,BC547,
"Q3, Q4, Q5, Q6",TO-220-3_Vertical-little-bigger pads,4,IRF540N,
"R1, R2, R48, R49",0805,4,47k,
"R10, R11, R78, R79",R_Axial_DIN0207_L6.3mm_D2.5mm_P10.16mm_Horizontal,4,R,
"R12, R13, R80, R81",1206,4,R,
"R14, R72",0805,2,39k,
"R15, R23, R24, R31, R32, R33, R34, R36, R40, R42, R44, R46, R5, R6, R7, R71, R73, R74, R75, R76, R77, R8, R9",0805,23,10k,
"R16, R52, R54, R55",0805,4,10R,
"R17, R30",2512,2,50m,
"R18, R20, R21, R22",0805,4,510R,
R19,0805,1,120R,
"R25, R26, R27, R29",0805,4,100K,
R28,2512,1,50mR,
"R3, R4, R50, R51",0805,4,22k,
"R35, R37, R43, R45, R47",0805,5,220R,
R38,2512,1,500m,
R39,0805,1,1k,
R41,0805,1,3k3,
R53,2512,1,100m,
"RV1, RV3",Potentiometer_ACP_CA9-V10_Vertical,2,10k,
U1,DFN-8-1EP_3x3mm_P0.5mm_EP1.65x2.38mm,1,LT4320xDD-1,
U10,TO-92_Inline_LITTLE_BIGGER,1,TL431LP,
"U14, U2",SOIC-16_3.9x9.9mm_P1.27mm,2,74HC595,
U3,SOIC-8_3.9x4.9mm_P1.27mm,1,ST485,
"U4, U7",VSSOP-10_3x3mm_P0.5mm,2,INA226,
U5,MSOP-12-1EP_3x4mm_P0.65mm_EP1.65x2.85mm,1,LT3652EMSE,
U6,SOIC-8_3.9x4.9mm_P1.27mm,1,LM358,
U8,DIP-8_W7.62mm,1,MC34063AP,
U9,SOIC-18W_7.5x11.6mm_P1.27mm,1,PIC16F819-ISO,
